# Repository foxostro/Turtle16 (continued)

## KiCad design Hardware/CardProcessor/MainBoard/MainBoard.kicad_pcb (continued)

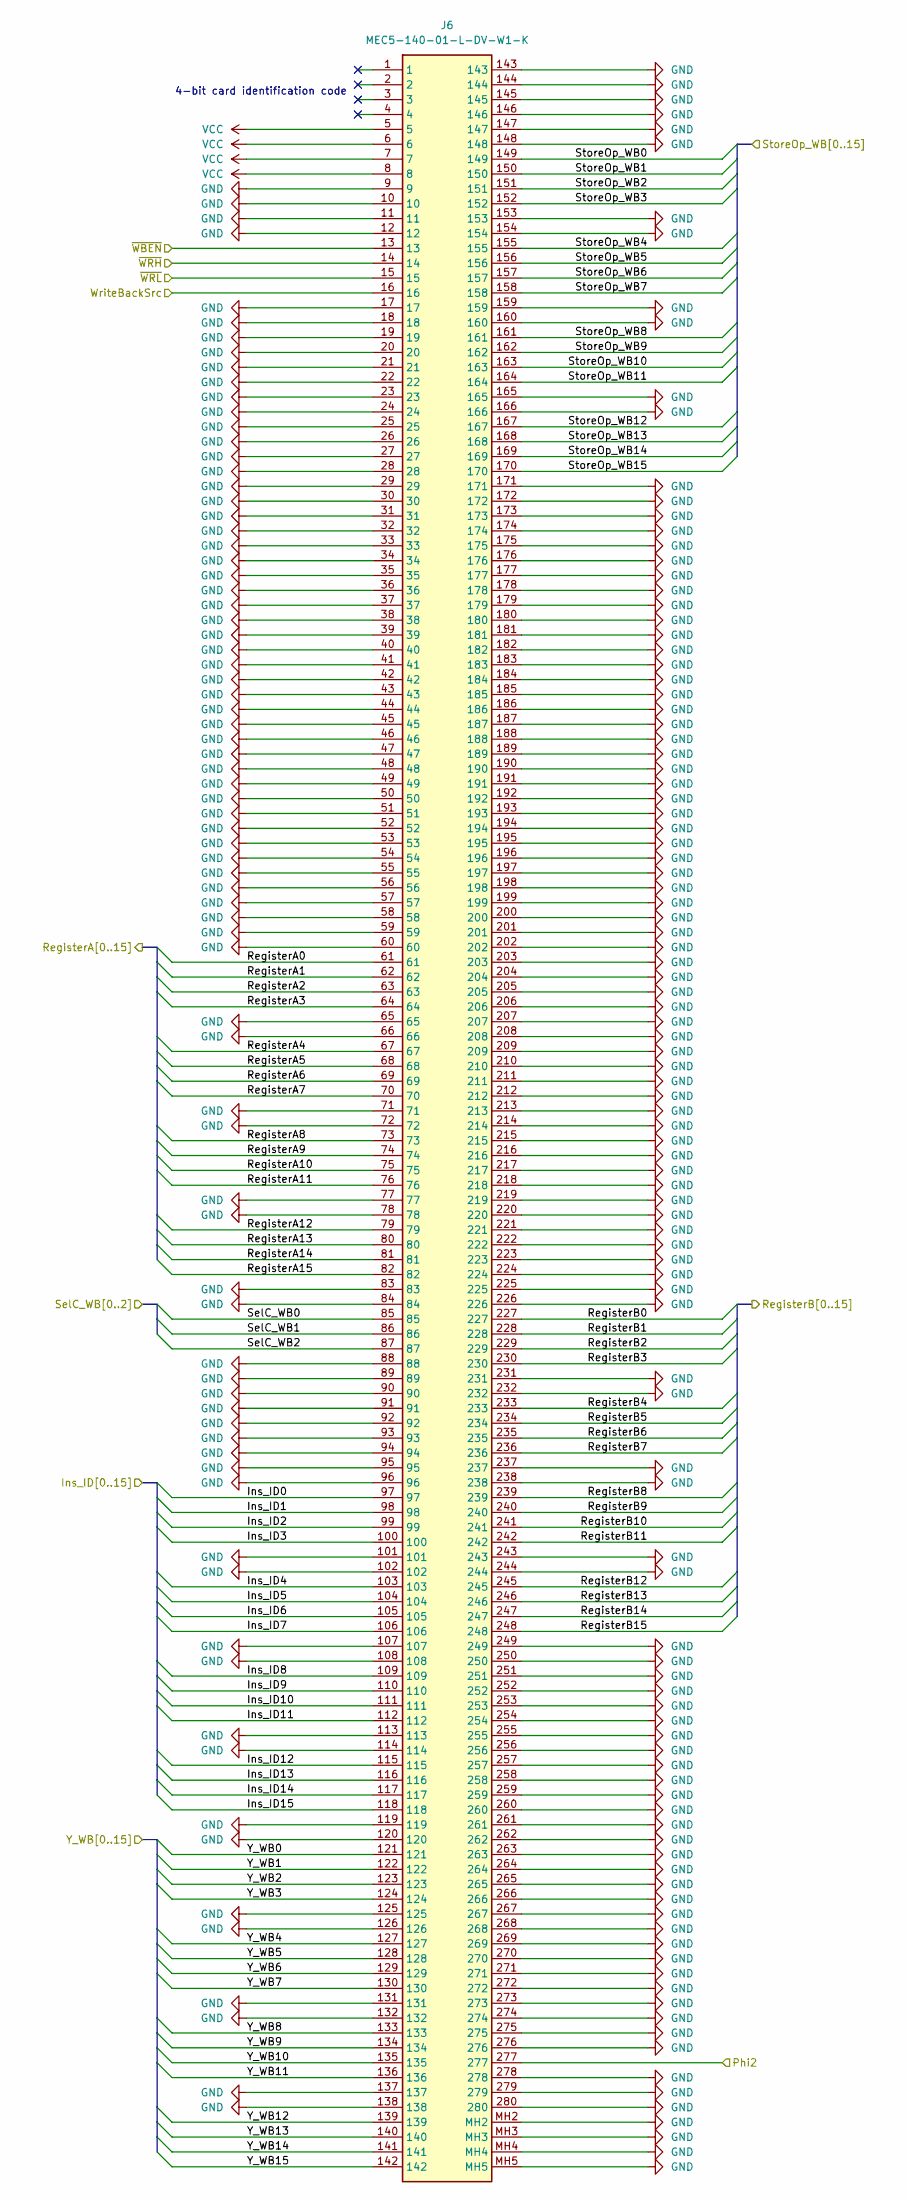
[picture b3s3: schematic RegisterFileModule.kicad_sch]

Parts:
J6: MEC5-140-01-L-DV-W1-K; MEC514001LDVW1K; Mouser Part Number 200-MEC514001LDVW1K

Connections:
/BypassModule/RegisterA0: J6.61; also elsewhere on the board
/BypassModule/RegisterA1: J6.62; also elsewhere on the board
/BypassModule/RegisterA2: J6.63; also elsewhere on the board
/BypassModule/RegisterA3: J6.64; also elsewhere on the board
/BypassModule/RegisterA4: J6.67; also elsewhere on the board
/BypassModule/RegisterA5: J6.68; also elsewhere on the board
/BypassModule/RegisterA6: J6.69; also elsewhere on the board
/BypassModule/RegisterA7: J6.70; also elsewhere on the board
/BypassModule/RegisterA8: J6.73; also elsewhere on the board
/BypassModule/RegisterA9: J6.74; also elsewhere on the board
/BypassModule/RegisterA10: J6.75; also elsewhere on the board
/BypassModule/RegisterA11: J6.76; also elsewhere on the board
/BypassModule/RegisterA12: J6.79; also elsewhere on the board
/BypassModule/RegisterA13: J6.80; also elsewhere on the board
/BypassModule/RegisterA14: J6.81; also elsewhere on the board
/BypassModule/RegisterA15: J6.82; also elsewhere on the board
/BypassModule/RegisterB0: J6.227; also elsewhere on the board
/BypassModule/RegisterB1: J6.228; also elsewhere on the board
/BypassModule/RegisterB2: J6.229; also elsewhere on the board
/BypassModule/RegisterB3: J6.230; also elsewhere on the board
/BypassModule/RegisterB4: J6.233; also elsewhere on the board
/BypassModule/RegisterB5: J6.234; also elsewhere on the board
/BypassModule/RegisterB6: J6.235; also elsewhere on the board
/BypassModule/RegisterB7: J6.236; also elsewhere on the board
/BypassModule/RegisterB8: J6.239; also elsewhere on the board
/BypassModule/RegisterB9: J6.240; also elsewhere on the board
/BypassModule/RegisterB10: J6.241; also elsewhere on the board
/BypassModule/RegisterB11: J6.242; also elsewhere on the board
/BypassModule/RegisterB12: J6.245; also elsewhere on the board
/BypassModule/RegisterB13: J6.246; also elsewhere on the board
/BypassModule/RegisterB14: J6.247; also elsewhere on the board
/BypassModule/RegisterB15: J6.248; also elsewhere on the board
/ControlModule/Ins_ID0: J6.97; also elsewhere on the board
/ControlModule/Ins_ID1: J6.98; also elsewhere on the board
/ControlModule/Ins_ID2: J6.99; also elsewhere on the board
/ControlModule/Ins_ID3: J6.100; also elsewhere on the board
/ControlModule/Ins_ID4: J6.103; also elsewhere on the board
/ControlModule/Ins_ID5: J6.104; also elsewhere on the board
/ControlModule/Ins_ID6: J6.105; also elsewhere on the board
/ControlModule/Ins_ID7: J6.106; also elsewhere on the board
/ControlModule/Ins_ID8: J6.109; also elsewhere on the board
/ControlModule/Ins_ID9: J6.110; also elsewhere on the board
/ControlModule/Ins_ID10: J6.111; also elsewhere on the board
/ControlModule/Ins_ID11: J6.112; also elsewhere on the board
/ControlModule/Ins_ID12: J6.115; also elsewhere on the board
/ControlModule/Ins_ID13: J6.116; also elsewhere on the board
/ControlModule/Ins_ID14: J6.117; also elsewhere on the board
/ControlModule/Ins_ID15: J6.118; also elsewhere on the board
/MEMModule/Ctl_WB17: J6.16; also elsewhere on the board
/MEMModule/Ctl_WB18: J6.15; also elsewhere on the board
/MEMModule/Ctl_WB19: J6.14; also elsewhere on the board
/MEMModule/Ctl_WB20: J6.13; also elsewhere on the board
/MEMModule/SelC_WB0: J6.85; also elsewhere on the board
/MEMModule/SelC_WB1: J6.86; also elsewhere on the board
/MEMModule/SelC_WB2: J6.87; also elsewhere on the board
/MEMModule/StoreOp_WB0: J6.149; also elsewhere on the board
/MEMModule/StoreOp_WB1: J6.150; also elsewhere on the board
/MEMModule/StoreOp_WB2: J6.151; also elsewhere on the board
/MEMModule/StoreOp_WB3: J6.152; also elsewhere on the board
/MEMModule/StoreOp_WB4: J6.155; also elsewhere on the board
/MEMModule/StoreOp_WB5: J6.156; also elsewhere on the board
/MEMModule/StoreOp_WB6: J6.157; also elsewhere on the board
/MEMModule/StoreOp_WB7: J6.158; also elsewhere on the board
/MEMModule/StoreOp_WB8: J6.161; also elsewhere on the board
/MEMModule/StoreOp_WB9: J6.162; also elsewhere on the board
/MEMModule/StoreOp_WB10: J6.163; also elsewhere on the board
/MEMModule/StoreOp_WB11: J6.164; also elsewhere on the board
/MEMModule/StoreOp_WB12: J6.167; also elsewhere on the board
/MEMModule/StoreOp_WB13: J6.168; also elsewhere on the board
/MEMModule/StoreOp_WB14: J6.169; also elsewhere on the board
/MEMModule/StoreOp_WB15: J6.170; also elsewhere on the board
/MEMModule/Y_WB0: J6.121; also elsewhere on the board
/MEMModule/Y_WB1: J6.122; also elsewhere on the board
/MEMModule/Y_WB2: J6.123; also elsewhere on the board
/MEMModule/Y_WB3: J6.124; also elsewhere on the board
/MEMModule/Y_WB4: J6.127; also elsewhere on the board
/MEMModule/Y_WB5: J6.128; also elsewhere on the board
/MEMModule/Y_WB6: J6.129; also elsewhere on the board
/MEMModule/Y_WB7: J6.130; also elsewhere on the board
/MEMModule/Y_WB8: J6.133; also elsewhere on the board
/MEMModule/Y_WB9: J6.134; also elsewhere on the board
/MEMModule/Y_WB10: J6.135; also elsewhere on the board
/MEMModule/Y_WB11: J6.136; also elsewhere on the board
/MEMModule/Y_WB12: J6.139; also elsewhere on the board
/MEMModule/Y_WB13: J6.140; also elsewhere on the board
/MEMModule/Y_WB14: J6.141; also elsewhere on the board
/MEMModule/Y_WB15: J6.142; also elsewhere on the board
/Phi2: J6.277; also elsewhere on the board
GND: J6.9, J6.10, J6.11, J6.12, J6.17, J6.18, J6.19, J6.20, J6.21, J6.22, J6.23, J6.24, J6.25, J6.26, J6.27, J6.28, J6.29, J6.30, J6.31, J6.32, J6.33, J6.34, J6.35, J6.36, J6.37, J6.38, J6.39, J6.40, J6.41, J6.42, J6.43, J6.44, J6.45, J6.46, J6.47, J6.48, J6.49, J6.50, J6.51, J6.52, J6.53, J6.54, J6.55, J6.56, J6.57, J6.58, J6.59, J6.60, J6.65, J6.66, J6.71, J6.72, J6.77, J6.78, J6.83, J6.84, J6.88, J6.89, J6.90, J6.91, J6.92, J6.93, J6.94, J6.95, J6.96, J6.101, J6.102, J6.107, J6.108, J6.113, J6.114, J6.119, J6.120, J6.125, J6.126, J6.131, J6.132, J6.137, J6.138, J6.143, J6.144, J6.145, J6.146, J6.147, J6.148, J6.153, J6.154, J6.159, J6.160, J6.165, J6.166, J6.171, J6.172, J6.173, J6.174, J6.175, J6.176, J6.177, J6.178, J6.179, J6.180, J6.181, J6.182, J6.183, J6.184, J6.185, J6.186, J6.187, J6.188, J6.189, J6.190, J6.191, J6.192, J6.193, J6.194, J6.195, J6.196, J6.197, J6.198, J6.199, J6.200, J6.201, J6.202, J6.203, J6.204, J6.205, J6.206, J6.207, J6.208, J6.209, J6.210, J6.211, J6.212, J6.213, J6.214, J6.215, J6.216, J6.217, J6.218, J6.219, J6.220, J6.221, J6.222, J6.223, J6.224, J6.225, J6.226, J6.231, J6.232, J6.237, J6.238, J6.243, J6.244, J6.249, J6.250, J6.251, J6.252, J6.253, J6.254, J6.255, J6.256, J6.257, J6.258, J6.259, J6.260, J6.261, J6.262, J6.263, J6.264, J6.265, J6.266, J6.267, J6.268, J6.269, J6.270, J6.271, J6.272, J6.273, J6.274, J6.275, J6.276, J6.278, J6.279, J6.280, J6.MH2, J6.MH3, J6.MH4, J6.MH5; also elsewhere on the board
VCC: J6.5, J6.6, J6.7, J6.8; also elsewhere on the board

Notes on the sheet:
4-bit card identification code

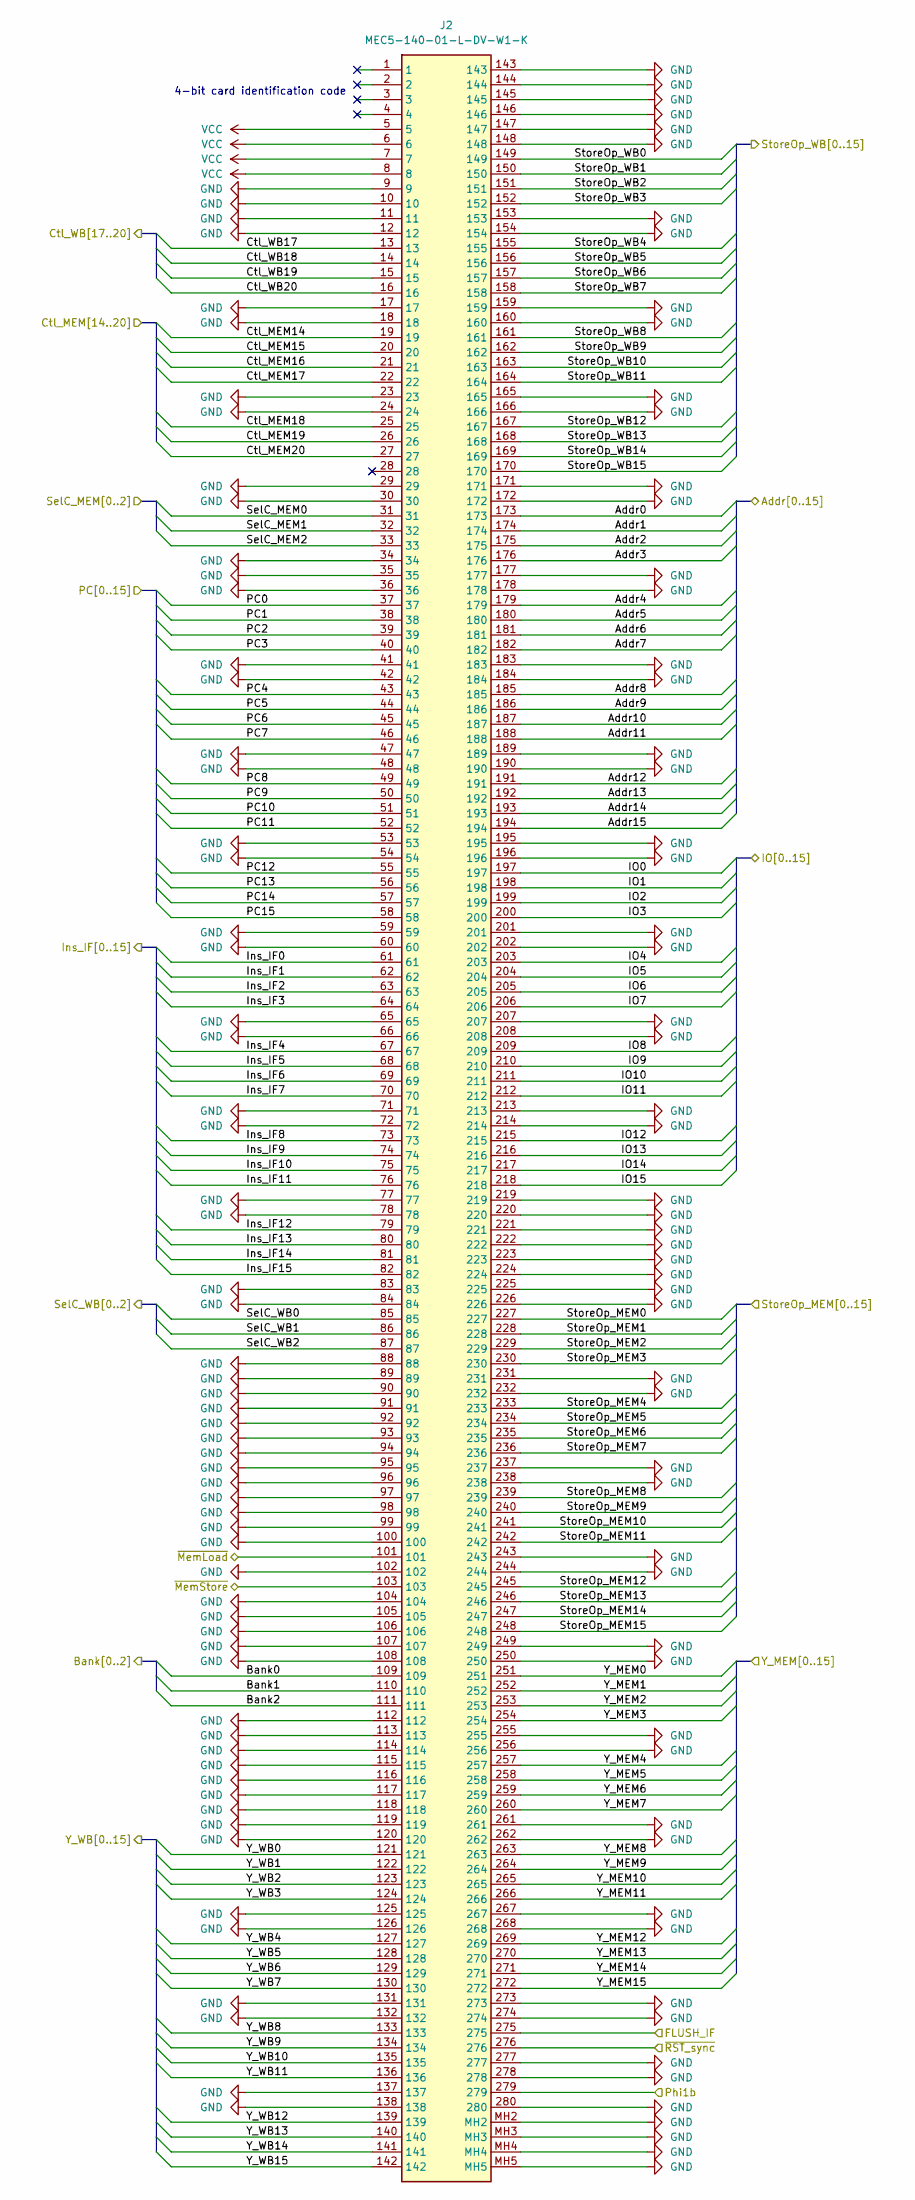
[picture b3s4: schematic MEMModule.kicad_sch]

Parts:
J2: MEC5-140-01-L-DV-W1-K; MEC514001LDVW1K; Mouser Part Number 200-MEC514001LDVW1K

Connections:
/Addr0: J2.173; also elsewhere on the board
/Addr1: J2.174; also elsewhere on the board
/Addr2: J2.175; also elsewhere on the board
/Addr3: J2.176; also elsewhere on the board
/Addr4: J2.179; also elsewhere on the board
/Addr5: J2.180; also elsewhere on the board
/Addr6: J2.181; also elsewhere on the board
/Addr7: J2.182; also elsewhere on the board
/Addr8: J2.185; also elsewhere on the board
/Addr9: J2.186; also elsewhere on the board
/Addr10: J2.187; also elsewhere on the board
/Addr11: J2.188; also elsewhere on the board
/Addr12: J2.191; also elsewhere on the board
/Addr13: J2.192; also elsewhere on the board
/Addr14: J2.193; also elsewhere on the board
/Addr15: J2.194; also elsewhere on the board
/Bank0: J2.109; also elsewhere on the board
/Bank1: J2.110; also elsewhere on the board
/Bank2: J2.111; also elsewhere on the board
/BypassModule/Y_MEM0: J2.251; also elsewhere on the board
/BypassModule/Y_MEM1: J2.252; also elsewhere on the board
/BypassModule/Y_MEM2: J2.253; also elsewhere on the board
/BypassModule/Y_MEM3: J2.254; also elsewhere on the board
/BypassModule/Y_MEM4: J2.257; also elsewhere on the board
/BypassModule/Y_MEM5: J2.258; also elsewhere on the board
/BypassModule/Y_MEM6: J2.259; also elsewhere on the board
/BypassModule/Y_MEM7: J2.260; also elsewhere on the board
/BypassModule/Y_MEM8: J2.263; also elsewhere on the board
/BypassModule/Y_MEM9: J2.264; also elsewhere on the board
/BypassModule/Y_MEM10: J2.265; also elsewhere on the board
/BypassModule/Y_MEM11: J2.266; also elsewhere on the board
/BypassModule/Y_MEM12: J2.269; also elsewhere on the board
/BypassModule/Y_MEM13: J2.270; also elsewhere on the board
/BypassModule/Y_MEM14: J2.271; also elsewhere on the board
/BypassModule/Y_MEM15: J2.272; also elsewhere on the board
/ControlModule/Ctl_MEM14: J2.19; also elsewhere on the board
/ControlModule/Ctl_MEM15: J2.20; also elsewhere on the board
/ControlModule/Ctl_MEM16: J2.21; also elsewhere on the board
/ControlModule/Ctl_MEM17: J2.22; also elsewhere on the board
/ControlModule/Ctl_MEM18: J2.25; also elsewhere on the board
/ControlModule/Ctl_MEM19: J2.26; also elsewhere on the board
/ControlModule/Ctl_MEM20: J2.27; also elsewhere on the board
/ControlModule/SelC_MEM0: J2.31; also elsewhere on the board
/ControlModule/SelC_MEM1: J2.32; also elsewhere on the board
/ControlModule/SelC_MEM2: J2.33; also elsewhere on the board
/EXModule/StoreOp_MEM0: J2.227; also elsewhere on the board
/EXModule/StoreOp_MEM1: J2.228; also elsewhere on the board
/EXModule/StoreOp_MEM2: J2.229; also elsewhere on the board
/EXModule/StoreOp_MEM3: J2.230; also elsewhere on the board
/EXModule/StoreOp_MEM4: J2.233; also elsewhere on the board
/EXModule/StoreOp_MEM5: J2.234; also elsewhere on the board
/EXModule/StoreOp_MEM6: J2.235; also elsewhere on the board
/EXModule/StoreOp_MEM7: J2.236; also elsewhere on the board
/EXModule/StoreOp_MEM8: J2.239; also elsewhere on the board
/EXModule/StoreOp_MEM9: J2.240; also elsewhere on the board
/EXModule/StoreOp_MEM10: J2.241; also elsewhere on the board
/EXModule/StoreOp_MEM11: J2.242; also elsewhere on the board
/EXModule/StoreOp_MEM12: J2.245; also elsewhere on the board
/EXModule/StoreOp_MEM13: J2.246; also elsewhere on the board
/EXModule/StoreOp_MEM14: J2.247; also elsewhere on the board
/EXModule/StoreOp_MEM15: J2.248; also elsewhere on the board
/IO0: J2.197; also elsewhere on the board
/IO1: J2.198; also elsewhere on the board
/IO2: J2.199; also elsewhere on the board
/IO3: J2.200; also elsewhere on the board
/IO4: J2.203; also elsewhere on the board
/IO5: J2.204; also elsewhere on the board
/IO6: J2.205; also elsewhere on the board
/IO7: J2.206; also elsewhere on the board
/IO8: J2.209; also elsewhere on the board
/IO9: J2.210; also elsewhere on the board
/IO10: J2.211; also elsewhere on the board
/IO11: J2.212; also elsewhere on the board
/IO12: J2.215; also elsewhere on the board
/IO13: J2.216; also elsewhere on the board
/IO14: J2.217; also elsewhere on the board
/IO15: J2.218; also elsewhere on the board
/MEMModule/Ctl_WB17: J2.13; also elsewhere on the board
/MEMModule/Ctl_WB18: J2.14; also elsewhere on the board
/MEMModule/Ctl_WB19: J2.15; also elsewhere on the board
/MEMModule/Ctl_WB20: J2.16; also elsewhere on the board
/MEMModule/FLUSH_IF: J2.275; also elsewhere on the board
/MEMModule/Ins_IF0: J2.61; also elsewhere on the board
/MEMModule/Ins_IF1: J2.62; also elsewhere on the board
/MEMModule/Ins_IF2: J2.63; also elsewhere on the board
/MEMModule/Ins_IF3: J2.64; also elsewhere on the board
/MEMModule/Ins_IF4: J2.67; also elsewhere on the board
/MEMModule/Ins_IF5: J2.68; also elsewhere on the board
/MEMModule/Ins_IF6: J2.69; also elsewhere on the board
/MEMModule/Ins_IF7: J2.70; also elsewhere on the board
/MEMModule/Ins_IF8: J2.73; also elsewhere on the board
/MEMModule/Ins_IF9: J2.74; also elsewhere on the board
/MEMModule/Ins_IF10: J2.75; also elsewhere on the board
/MEMModule/Ins_IF11: J2.76; also elsewhere on the board
/MEMModule/Ins_IF12: J2.79; also elsewhere on the board
/MEMModule/Ins_IF13: J2.80; also elsewhere on the board
/MEMModule/Ins_IF14: J2.81; also elsewhere on the board
/MEMModule/Ins_IF15: J2.82; also elsewhere on the board
/MEMModule/PC0: J2.37; also elsewhere on the board
/MEMModule/PC1: J2.38; also elsewhere on the board
/MEMModule/PC2: J2.39; also elsewhere on the board
/MEMModule/PC3: J2.40; also elsewhere on the board
/MEMModule/PC4: J2.43; also elsewhere on the board
/MEMModule/PC5: J2.44; also elsewhere on the board
/MEMModule/PC6: J2.45; also elsewhere on the board
/MEMModule/PC7: J2.46; also elsewhere on the board
/MEMModule/PC8: J2.49; also elsewhere on the board
/MEMModule/PC9: J2.50; also elsewhere on the board
/MEMModule/PC10: J2.51; also elsewhere on the board
/MEMModule/PC11: J2.52; also elsewhere on the board
/MEMModule/PC12: J2.55; also elsewhere on the board
/MEMModule/PC13: J2.56; also elsewhere on the board
/MEMModule/PC14: J2.57; also elsewhere on the board
/MEMModule/PC15: J2.58; also elsewhere on the board
/MEMModule/SelC_WB0: J2.85; also elsewhere on the board
/MEMModule/SelC_WB1: J2.86; also elsewhere on the board
/MEMModule/SelC_WB2: J2.87; also elsewhere on the board
/MEMModule/StoreOp_WB0: J2.149; also elsewhere on the board
/MEMModule/StoreOp_WB1: J2.150; also elsewhere on the board
/MEMModule/StoreOp_WB2: J2.151; also elsewhere on the board
/MEMModule/StoreOp_WB3: J2.152; also elsewhere on the board
/MEMModule/StoreOp_WB4: J2.155; also elsewhere on the board
/MEMModule/StoreOp_WB5: J2.156; also elsewhere on the board
/MEMModule/StoreOp_WB6: J2.157; also elsewhere on the board
/MEMModule/StoreOp_WB7: J2.158; also elsewhere on the board
/MEMModule/StoreOp_WB8: J2.161; also elsewhere on the board
/MEMModule/StoreOp_WB9: J2.162; also elsewhere on the board
/MEMModule/StoreOp_WB10: J2.163; also elsewhere on the board
/MEMModule/StoreOp_WB11: J2.164; also elsewhere on the board
/MEMModule/StoreOp_WB12: J2.167; also elsewhere on the board
/MEMModule/StoreOp_WB13: J2.168; also elsewhere on the board
/MEMModule/StoreOp_WB14: J2.169; also elsewhere on the board
/MEMModule/StoreOp_WB15: J2.170; also elsewhere on the board
/MEMModule/Y_WB0: J2.121; also elsewhere on the board
/MEMModule/Y_WB1: J2.122; also elsewhere on the board
/MEMModule/Y_WB2: J2.123; also elsewhere on the board
/MEMModule/Y_WB3: J2.124; also elsewhere on the board
/MEMModule/Y_WB4: J2.127; also elsewhere on the board
/MEMModule/Y_WB5: J2.128; also elsewhere on the board
/MEMModule/Y_WB6: J2.129; also elsewhere on the board
/MEMModule/Y_WB7: J2.130; also elsewhere on the board
/MEMModule/Y_WB8: J2.133; also elsewhere on the board
/MEMModule/Y_WB9: J2.134; also elsewhere on the board
/MEMModule/Y_WB10: J2.135; also elsewhere on the board
/MEMModule/Y_WB11: J2.136; also elsewhere on the board
/MEMModule/Y_WB12: J2.139; also elsewhere on the board
/MEMModule/Y_WB13: J2.140; also elsewhere on the board
/MEMModule/Y_WB14: J2.141; also elsewhere on the board
/MEMModule/Y_WB15: J2.142; also elsewhere on the board
/Phi1b: J2.279; also elsewhere on the board
/~MemLoad: J2.101; also elsewhere on the board
/~MemStore: J2.103; also elsewhere on the board
/~RST_sync: J2.276; also elsewhere on the board
GND: J2.9, J2.10, J2.11, J2.12, J2.17, J2.18, J2.23, J2.24, J2.29, J2.30, J2.34, J2.35, J2.36, J2.41, J2.42, J2.47, J2.48, J2.53, J2.54, J2.59, J2.60, J2.65, J2.66, J2.71, J2.72, J2.77, J2.78, J2.83, J2.84, J2.88, J2.89, J2.90, J2.91, J2.92, J2.93, J2.94, J2.95, J2.96, J2.97, J2.98, J2.99, J2.100, J2.102, J2.104, J2.105, J2.106, J2.107, J2.108, J2.112, J2.113, J2.114, J2.115, J2.116, J2.117, J2.118, J2.119, J2.120, J2.125, J2.126, J2.131, J2.132, J2.137, J2.138, J2.143, J2.144, J2.145, J2.146, J2.147, J2.148, J2.153, J2.154, J2.159, J2.160, J2.165, J2.166, J2.171, J2.172, J2.177, J2.178, J2.183, J2.184, J2.189, J2.190, J2.195, J2.196, J2.201, J2.202, J2.207, J2.208, J2.213, J2.214, J2.219, J2.220, J2.221, J2.222, J2.223, J2.224, J2.225, J2.226, J2.231, J2.232, J2.237, J2.238, J2.243, J2.244, J2.249, J2.250, J2.255, J2.256, J2.261, J2.262, J2.267, J2.268, J2.273, J2.274, J2.277, J2.278, J2.280, J2.MH2, J2.MH3, J2.MH4, J2.MH5; also elsewhere on the board
VCC: J2.5, J2.6, J2.7, J2.8; also elsewhere on the board

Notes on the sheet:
4-bit card identification code

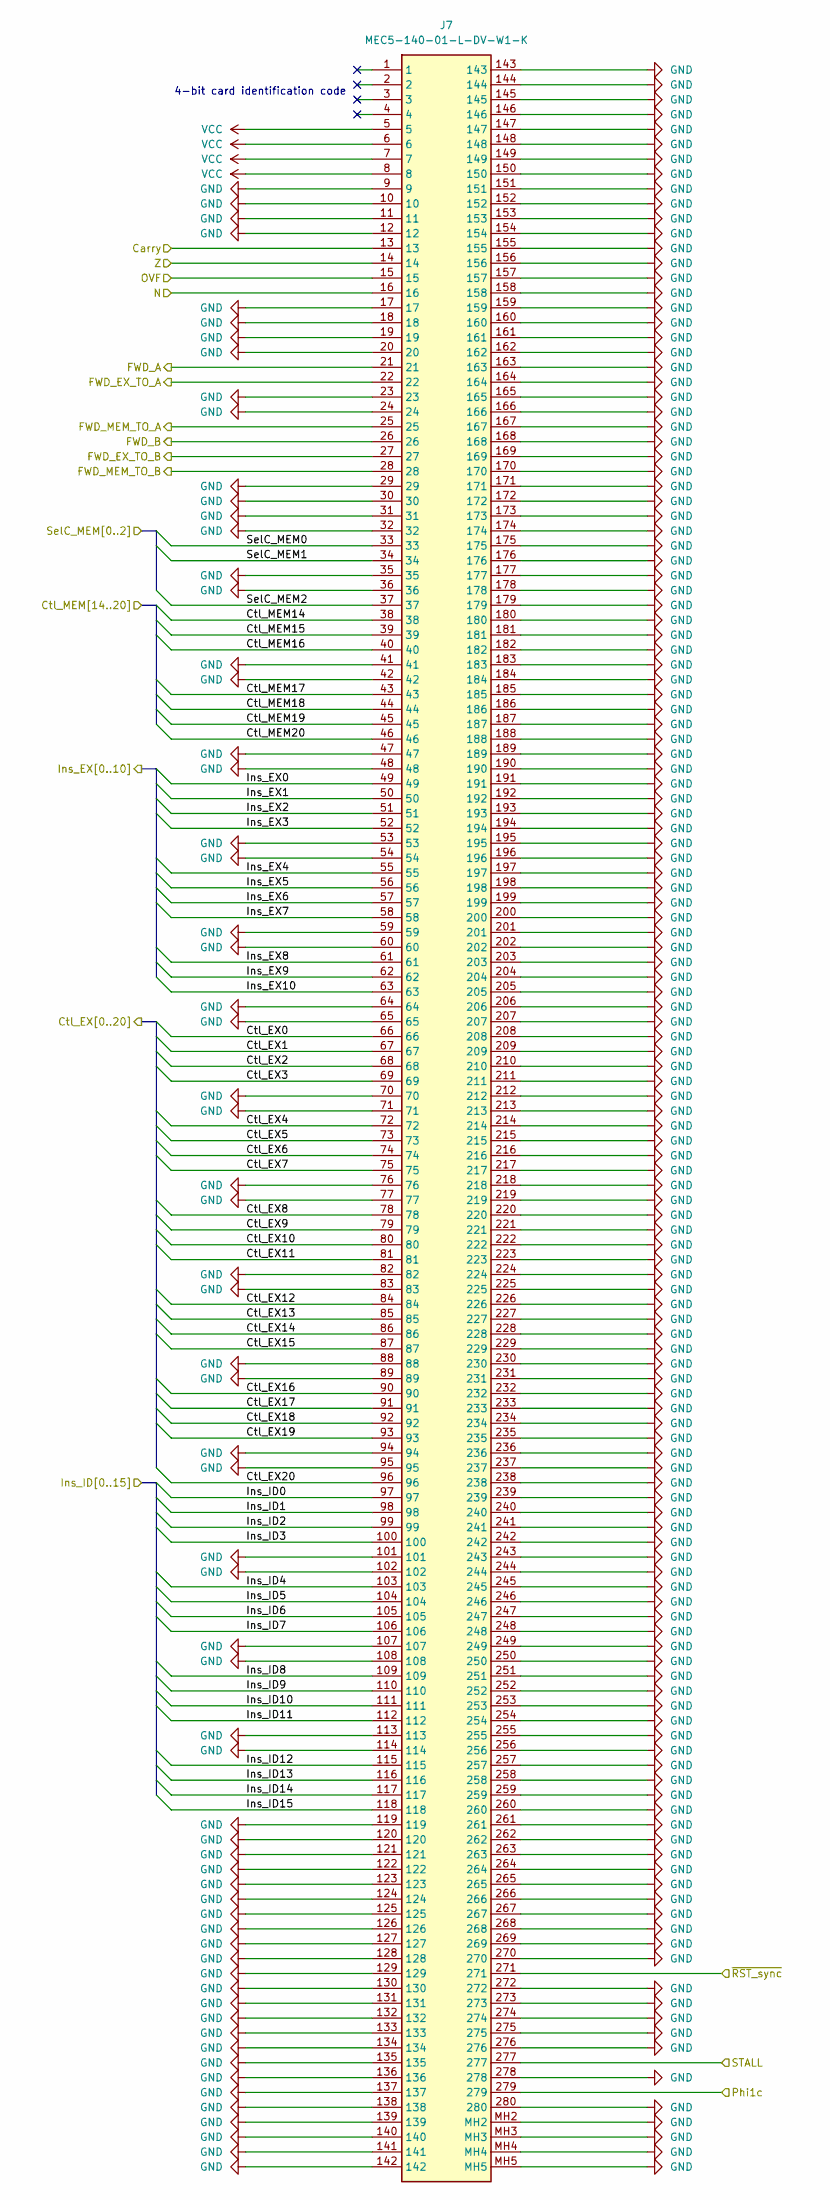
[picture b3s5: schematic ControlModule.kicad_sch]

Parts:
J7: MEC5-140-01-L-DV-W1-K; MEC514001LDVW1K; Mouser Part Number 200-MEC514001LDVW1K

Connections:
/BypassModule/FWD_A: J7.21; also elsewhere on the board
/BypassModule/FWD_B: J7.26; also elsewhere on the board
/BypassModule/FWD_EX_TO_A: J7.22; also elsewhere on the board
/BypassModule/FWD_EX_TO_B: J7.27; also elsewhere on the board
/BypassModule/FWD_MEM_TO_A: J7.25; also elsewhere on the board
/BypassModule/FWD_MEM_TO_B: J7.28; also elsewhere on the board
/ControlModule/Carry: J7.13; also elsewhere on the board
/ControlModule/Ctl_EX0: J7.66; also elsewhere on the board
/ControlModule/Ctl_EX1: J7.67; also elsewhere on the board
/ControlModule/Ctl_EX2: J7.68; also elsewhere on the board
/ControlModule/Ctl_EX3: J7.69; also elsewhere on the board
/ControlModule/Ctl_EX4: J7.72; also elsewhere on the board
/ControlModule/Ctl_EX5: J7.73; also elsewhere on the board
/ControlModule/Ctl_EX6: J7.74; also elsewhere on the board
/ControlModule/Ctl_EX7: J7.75; also elsewhere on the board
/ControlModule/Ctl_EX8: J7.78; also elsewhere on the board
/ControlModule/Ctl_EX9: J7.79; also elsewhere on the board
/ControlModule/Ctl_EX10: J7.80; also elsewhere on the board
/ControlModule/Ctl_EX11: J7.81; also elsewhere on the board
/ControlModule/Ctl_EX12: J7.84; also elsewhere on the board
/ControlModule/Ctl_EX13: J7.85; also elsewhere on the board
/ControlModule/Ctl_EX14: J7.86; also elsewhere on the board
/ControlModule/Ctl_EX15: J7.87; also elsewhere on the board
/ControlModule/Ctl_EX16: J7.90; also elsewhere on the board
/ControlModule/Ctl_EX17: J7.91; also elsewhere on the board
/ControlModule/Ctl_EX18: J7.92; also elsewhere on the board
/ControlModule/Ctl_EX19: J7.93; also elsewhere on the board
/ControlModule/Ctl_EX20: J7.96; also elsewhere on the board
/ControlModule/Ctl_MEM14: J7.38; also elsewhere on the board
/ControlModule/Ctl_MEM15: J7.39; also elsewhere on the board
/ControlModule/Ctl_MEM16: J7.40; also elsewhere on the board
/ControlModule/Ctl_MEM17: J7.43; also elsewhere on the board
/ControlModule/Ctl_MEM18: J7.44; also elsewhere on the board
/ControlModule/Ctl_MEM19: J7.45; also elsewhere on the board
/ControlModule/Ctl_MEM20: J7.46; also elsewhere on the board
/ControlModule/Ins_EX0: J7.49; also elsewhere on the board
/ControlModule/Ins_EX1: J7.50; also elsewhere on the board
/ControlModule/Ins_EX2: J7.51; also elsewhere on the board
/ControlModule/Ins_EX3: J7.52; also elsewhere on the board
/ControlModule/Ins_EX4: J7.55; also elsewhere on the board
/ControlModule/Ins_EX5: J7.56; also elsewhere on the board
/ControlModule/Ins_EX6: J7.57; also elsewhere on the board
/ControlModule/Ins_EX7: J7.58; also elsewhere on the board
/ControlModule/Ins_EX8: J7.61; also elsewhere on the board
/ControlModule/Ins_EX9: J7.62; also elsewhere on the board
/ControlModule/Ins_EX10: J7.63; also elsewhere on the board
/ControlModule/Ins_ID0: J7.97; also elsewhere on the board
/ControlModule/Ins_ID1: J7.98; also elsewhere on the board
/ControlModule/Ins_ID2: J7.99; also elsewhere on the board
/ControlModule/Ins_ID3: J7.100; also elsewhere on the board
/ControlModule/Ins_ID4: J7.103; also elsewhere on the board
/ControlModule/Ins_ID5: J7.104; also elsewhere on the board
/ControlModule/Ins_ID6: J7.105; also elsewhere on the board
/ControlModule/Ins_ID7: J7.106; also elsewhere on the board
/ControlModule/Ins_ID8: J7.109; also elsewhere on the board
/ControlModule/Ins_ID9: J7.110; also elsewhere on the board
/ControlModule/Ins_ID10: J7.111; also elsewhere on the board
/ControlModule/Ins_ID11: J7.112; also elsewhere on the board
/ControlModule/Ins_ID12: J7.115; also elsewhere on the board
/ControlModule/Ins_ID13: J7.116; also elsewhere on the board
/ControlModule/Ins_ID14: J7.117; also elsewhere on the board
/ControlModule/Ins_ID15: J7.118; also elsewhere on the board
/ControlModule/N: J7.16; also elsewhere on the board
/ControlModule/OVF: J7.15; also elsewhere on the board
/ControlModule/STALL: J7.277; also elsewhere on the board
/ControlModule/SelC_MEM0: J7.33; also elsewhere on the board
/ControlModule/SelC_MEM1: J7.34; also elsewhere on the board
/ControlModule/SelC_MEM2: J7.37; also elsewhere on the board
/ControlModule/Z: J7.14; also elsewhere on the board
/Phi1c: J7.279; also elsewhere on the board
/~RST_sync: J7.271; also elsewhere on the board
GND: J7.9, J7.10, J7.11, J7.12, J7.17, J7.18, J7.19, J7.20, J7.23, J7.24, J7.29, J7.30, J7.31, J7.32, J7.35, J7.36, J7.41, J7.42, J7.47, J7.48, J7.53, J7.54, J7.59, J7.60, J7.64, J7.65, J7.70, J7.71, J7.76, J7.77, J7.82, J7.83, J7.88, J7.89, J7.94, J7.95, J7.101, J7.102, J7.107, J7.108, J7.113, J7.114, J7.119, J7.120, J7.121, J7.122, J7.123, J7.124, J7.125, J7.126, J7.127, J7.128, J7.129, J7.130, J7.131, J7.132, J7.133, J7.134, J7.135, J7.136, J7.137, J7.138, J7.139, J7.140, J7.141, J7.142, J7.143, J7.144, J7.145, J7.146, J7.147, J7.148, J7.149, J7.150, J7.151, J7.152, J7.153, J7.154, J7.155, J7.156, J7.157, J7.158, J7.159, J7.160, J7.161, J7.162, J7.163, J7.164, J7.165, J7.166, J7.167, J7.168, J7.169, J7.170, J7.171, J7.172, J7.173, J7.174, J7.175, J7.176, J7.177, J7.178, J7.179, J7.180, J7.181, J7.182, J7.183, J7.184, J7.185, J7.186, J7.187, J7.188, J7.189, J7.190, J7.191, J7.192, J7.193, J7.194, J7.195, J7.196, J7.197, J7.198, J7.199, J7.200, J7.201, J7.202, J7.203, J7.204, J7.205, J7.206, J7.207, J7.208, J7.209, J7.210, J7.211, J7.212, J7.213, J7.214, J7.215, J7.216, J7.217, J7.218, J7.219, J7.220, J7.221, J7.222, J7.223, J7.224, J7.225, J7.226, J7.227, J7.228, J7.229, J7.230, J7.231, J7.232, J7.233, J7.234, J7.235, J7.236, J7.237, J7.238, J7.239, J7.240, J7.241, J7.242, J7.243, J7.244, J7.245, J7.246, J7.247, J7.248, J7.249, J7.250, J7.251, J7.252, J7.253, J7.254, J7.255, J7.256, J7.257, J7.258, J7.259, J7.260, J7.261, J7.262, J7.263, J7.264, J7.265, J7.266, J7.267, J7.268, J7.269, J7.270, J7.272, J7.273, J7.274, J7.275, J7.276, J7.278, J7.280, J7.MH2, J7.MH3, J7.MH4, J7.MH5; also elsewhere on the board
VCC: J7.5, J7.6, J7.7, J7.8; also elsewhere on the board

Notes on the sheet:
4-bit card identification code
